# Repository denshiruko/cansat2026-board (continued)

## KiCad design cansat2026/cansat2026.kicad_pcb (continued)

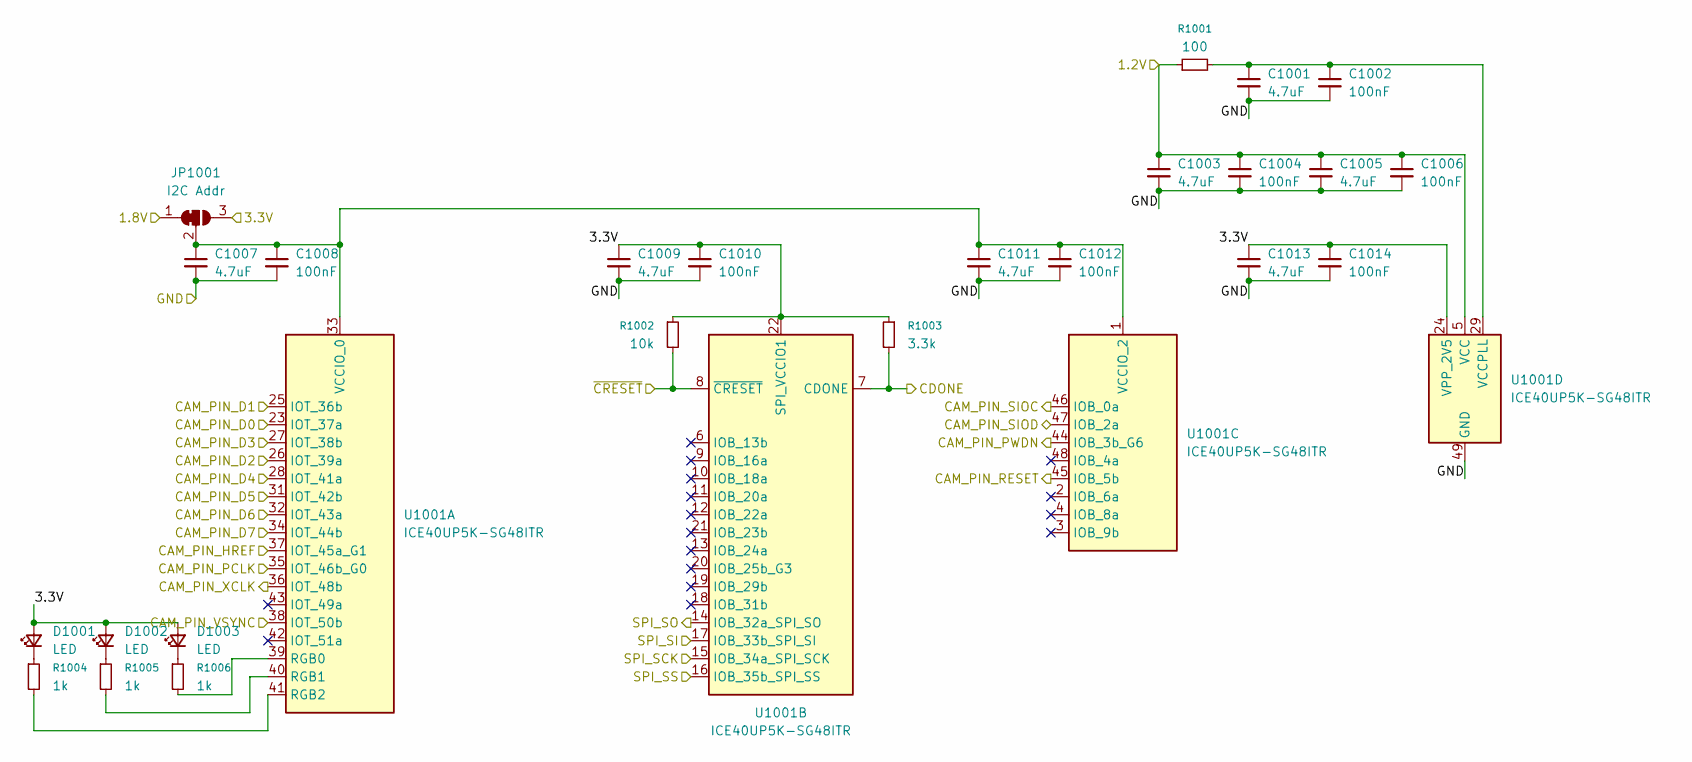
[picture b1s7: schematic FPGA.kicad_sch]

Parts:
C1001, C1003, C1005, C1007, C1009, C1011, C1013: 4.7uF; C_0402_1005Metric; LCSC Part C23733
C1002, C1004, C1006, C1008, C1010, C1012, C1014: 100nF; C_0402_1005Metric; LCSC Part C1525
D1001, D1002, D1003: LED; LED_0603_1608Metric
JP1001: I2C Addr; SolderJumper-3_P1.3mm_Bridged12_RoundedPad1.0x1.5mm_NumberL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
R1001: 100; R_0402_1005Metric; LCSC Part C25076
R1002: 10k; R_0402_1005Metric; LCSC Part C25744
R1003: 3.3k; R_0402_1005Metric; LCSC Part C25890
R1004, R1005, R1006: 1k; R_0402_1005Metric; LCSC Part C11702
U1001: ICE40UP5K-SG48ITR; QFN-48-1EP_7x7mm_P0.5mm_EP5.6x5.6mm; LCSC Part C2678152

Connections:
/1.2V: C1003.1, C1004.1, C1005.1, C1006.1, R1001.1, U1001.5 (VCC), U1001.30 (VCC); also elsewhere on the board
/1.8V: JP1001.1 (A); also elsewhere on the board
/CAM_PIN_D0: U1001.23 (IOT_37a); also elsewhere on the board
/CAM_PIN_D1: U1001.25 (IOT_36b); also elsewhere on the board
/CAM_PIN_D2: U1001.26 (IOT_39a); also elsewhere on the board
/CAM_PIN_D3: U1001.27 (IOT_38b); also elsewhere on the board
/CAM_PIN_D4: U1001.28 (IOT_41a); also elsewhere on the board
/CAM_PIN_D5: U1001.31 (IOT_42b); also elsewhere on the board
/CAM_PIN_D6: U1001.32 (IOT_43a); also elsewhere on the board
/CAM_PIN_D7: U1001.34 (IOT_44b); also elsewhere on the board
/CAM_PIN_HREF: U1001.37 (IOT_45a_G1); also elsewhere on the board
/CAM_PIN_PCLK: U1001.35 (IOT_46b_G0); also elsewhere on the board
/CAM_PIN_PWDN: U1001.44 (IOB_3b_G6); also elsewhere on the board
/CAM_PIN_RESET: U1001.45 (IOB_5b); also elsewhere on the board
/CAM_PIN_SIOC: U1001.46 (IOB_0a); also elsewhere on the board
/CAM_PIN_SIOD: U1001.47 (IOB_2a); also elsewhere on the board
/CAM_PIN_VSYNC: U1001.38 (IOT_50b); also elsewhere on the board
/CAM_PIN_XCLK: U1001.36 (IOT_48b); also elsewhere on the board
/MCU/FPGA_CDONE: R1003.2, U1001.7 (CDONE); also elsewhere on the board
/MCU/FPGA_SPI_MISO: U1001.14 (IOB_32a_SPI_SO); also elsewhere on the board
/MCU/FPGA_SPI_MOSI: U1001.17 (IOB_33b_SPI_SI); also elsewhere on the board
/MCU/FPGA_SPI_SCK: U1001.15 (IOB_34a_SPI_SCK); also elsewhere on the board
/MCU/FPGA_SPI_SS: U1001.16 (IOB_35b_SPI_SS); also elsewhere on the board
/MCU/FPGA_~CRESET: R1002.2, U1001.8 (~CRESET); also elsewhere on the board
/VCC: C1009.1, C1010.1, C1013.1, C1014.1, D1001.2 (A), D1002.2 (A), D1003.2 (A), JP1001.3 (B), R1002.1, R1003.1, U1001.22 (SPI_VCCIO1), U1001.24 (VPP_2V5); also elsewhere on the board
GND: C1001.2, C1002.2, C1003.2, C1004.2, C1005.2, C1006.2, C1007.2, C1008.2, C1009.2, C1010.2, C1011.2, C1012.2, C1013.2, C1014.2, U1001.49 (GND); also elsewhere on the board
unnamed: D1001.1 (K), R1004.1
unnamed: D1002.1 (K), R1005.1
unnamed: D1003.1 (K), R1006.1
unnamed: C1007.1, C1008.1, C1011.1, C1012.1, JP1001.2 (C), U1001.1 (VCCIO_2), U1001.33 (VCCIO_0)
unnamed: R1006.2, U1001.39 (RGB0)
unnamed: R1005.2, U1001.40 (RGB1)
unnamed: R1004.2, U1001.41 (RGB2)
unnamed: C1001.1, C1002.1, R1001.2, U1001.29 (VCCPLL)

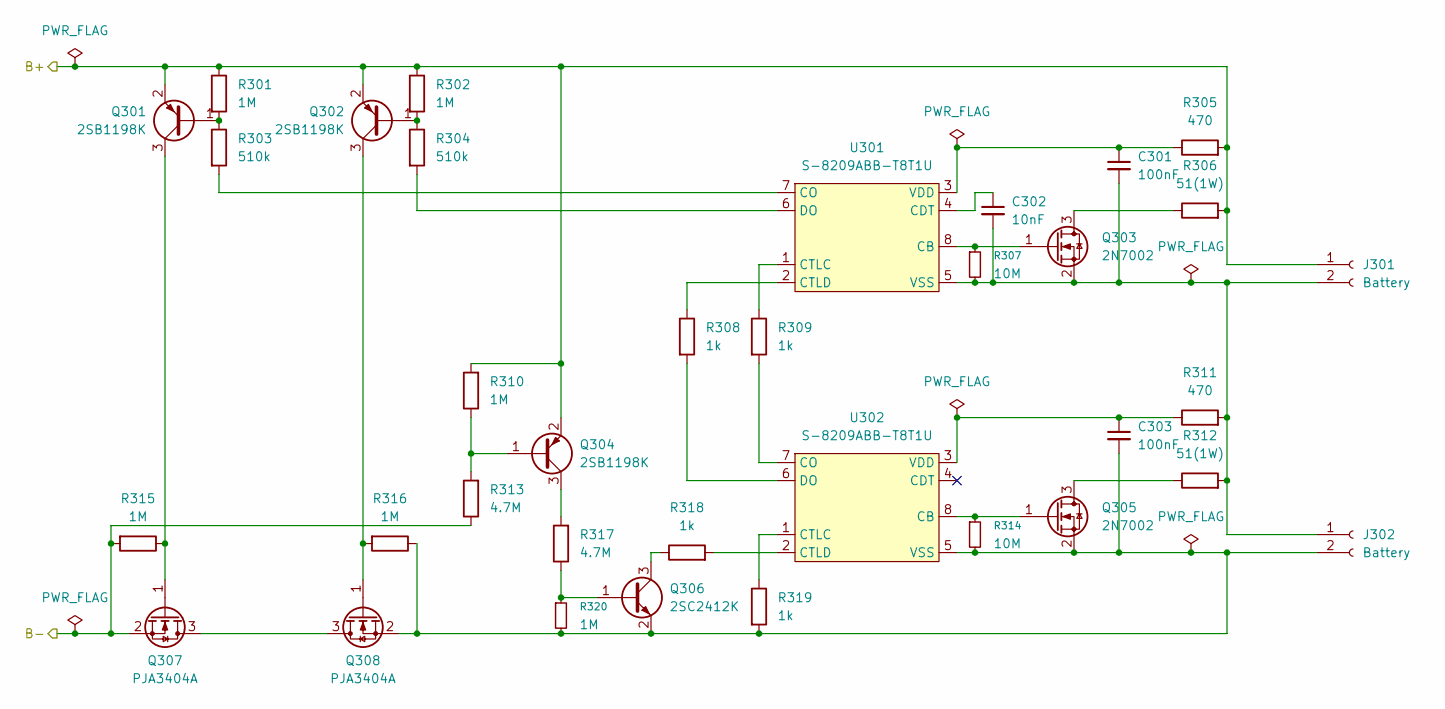
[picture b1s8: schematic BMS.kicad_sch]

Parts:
C301, C303: 100nF; C_0402_1005Metric; LCSC Part C1525
C302: 10nF; C_0402_1005Metric; LCSC Part C15195
J301, J302: Battery; JST_VH_B2P-VH_1x02_P3.96mm_Vertical
Q301, Q302, Q304: 2SB1198K; SC-59; LCSC Part C266246
Q303, Q305: 2N7002; SOT-23; LCSC Part C8545
Q306: 2SC2412K; SC-59; LCSC Part C111699
Q307, Q308: PJA3404A; SOT-23; Mouser Part 241-PJA3404AR100001
R301, R302, R310, R315, R316, R320: 1M; R_0402_1005Metric; LCSC Part C26083
R303, R304: 510k; R_0402_1005Metric; LCSC Part C11616
R305, R311: 470; R_0402_1005Metric; LCSC Part C25117
R306, R312: 51(1W); R_1206_3216Metric; Mouser Part 660-SG73S2BTTD51R0F
R307, R314: 10M; R_0603_1608Metric; LCSC Part C7250
R308, R309, R318, R319: 1k; R_0402_1005Metric; LCSC Part C11702
R313, R317: 4.7M; R_0603_1608Metric; LCSC Part C23163
U301, U302: S-8209ABB-T8T1U; TSSOP-8_4.4x3mm_P0.65mm; Mouser Part 628-S-8209ABB-T8T1U

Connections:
/Power/BATT+: J301.1, Q301.2, Q302.2, Q304.2, R301.1, R302.1, R305.2, R306.2, R310.2; also elsewhere on the board
GND: Q307.2 (S), R313.1, R315.2; also elsewhere on the board
unnamed: C301.2, C302.2, J301.2, J302.1, Q303.2 (S), R307.2, R311.2, R312.2, U301.5 (VSS)
unnamed: C303.2, J302.2, Q305.2 (S), Q306.2, Q308.2 (S), R314.2, R316.1, R319.2, R320.2, U302.5 (VSS)
unnamed: Q301.1, R301.2, R303.1
unnamed: Q302.1, R302.2, R304.1
unnamed: Q303.3 (D), R306.1
unnamed: Q303.1 (G), R307.1, U301.8 (CB)
unnamed: Q304.1, R310.1, R313.2
unnamed: Q304.3, R317.2
unnamed: Q305.3 (D), R312.1
unnamed: Q305.1 (G), R314.1, U302.8 (CB)
unnamed: Q306.1, R317.1, R320.1
unnamed: Q306.3, R318.1
unnamed: Q307.3 (D), Q308.3 (D)
unnamed: Q301.3, Q307.1 (G), R315.1
unnamed: Q302.3, Q308.1 (G), R316.2
unnamed: C302.1, U301.4 (CDT)
unnamed: R303.2, U301.7 (CO)
unnamed: R309.1, U301.1 (CTLC)
unnamed: R308.1, U301.2 (CTLD)
unnamed: R304.2, U301.6 (DO)
unnamed: C301.1, R305.1, U301.3 (VDD)
unnamed: R309.2, U302.7 (CO)
unnamed: R319.1, U302.1 (CTLC)
unnamed: R318.2, U302.2 (CTLD)
unnamed: R308.2, U302.6 (DO)
unnamed: C303.1, R311.1, U302.3 (VDD)

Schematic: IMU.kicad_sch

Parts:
C701, C702: 100nF; C_0402_1005Metric; LCSC Part C1525
JP701: I2C Addr; SolderJumper-3_P1.3mm_Bridged12_RoundedPad1.0x1.5mm_NumberL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
U701: LSM6DSV; LGA-14_3x2.5mm_P0.5mm_LayoutBorder3x4y

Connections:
/I2C1SCL: U701.13 (SCL); also elsewhere on the board
/I2C1SDA: U701.14 (SDA); also elsewhere on the board
/VCC: C701.1, C702.1, JP701.1 (A), U701.5 (VDDIO), U701.8 (VDD), U701.12 (CS); also elsewhere on the board
GND: C701.2, C702.2, JP701.3 (B), U701.2 (SDX), U701.3 (SCX), U701.6 (GND), U701.7 (GND); also elsewhere on the board
unnamed: JP701.2 (C), U701.1 (SDO/SA0)

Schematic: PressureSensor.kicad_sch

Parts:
C601: 100nF; C_0402_1005Metric; LCSC Part C1525
JP601: I2C Addr; SolderJumper-3_P1.3mm_Bridged12_RoundedPad1.0x1.5mm_NumberL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
U601: HP203B; LCSC Part C138665

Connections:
/I2C1SCL: U601.5 (SCL); also elsewhere on the board
/I2C1SDA: U601.6 (SDA); also elsewhere on the board
/VCC: C601.1, JP601.3 (B), U601.3 (VDD); also elsewhere on the board
GND: C601.2, JP601.1 (A), U601.2 (GND); also elsewhere on the board
unnamed: JP601.2 (C), U601.8 (CSB)

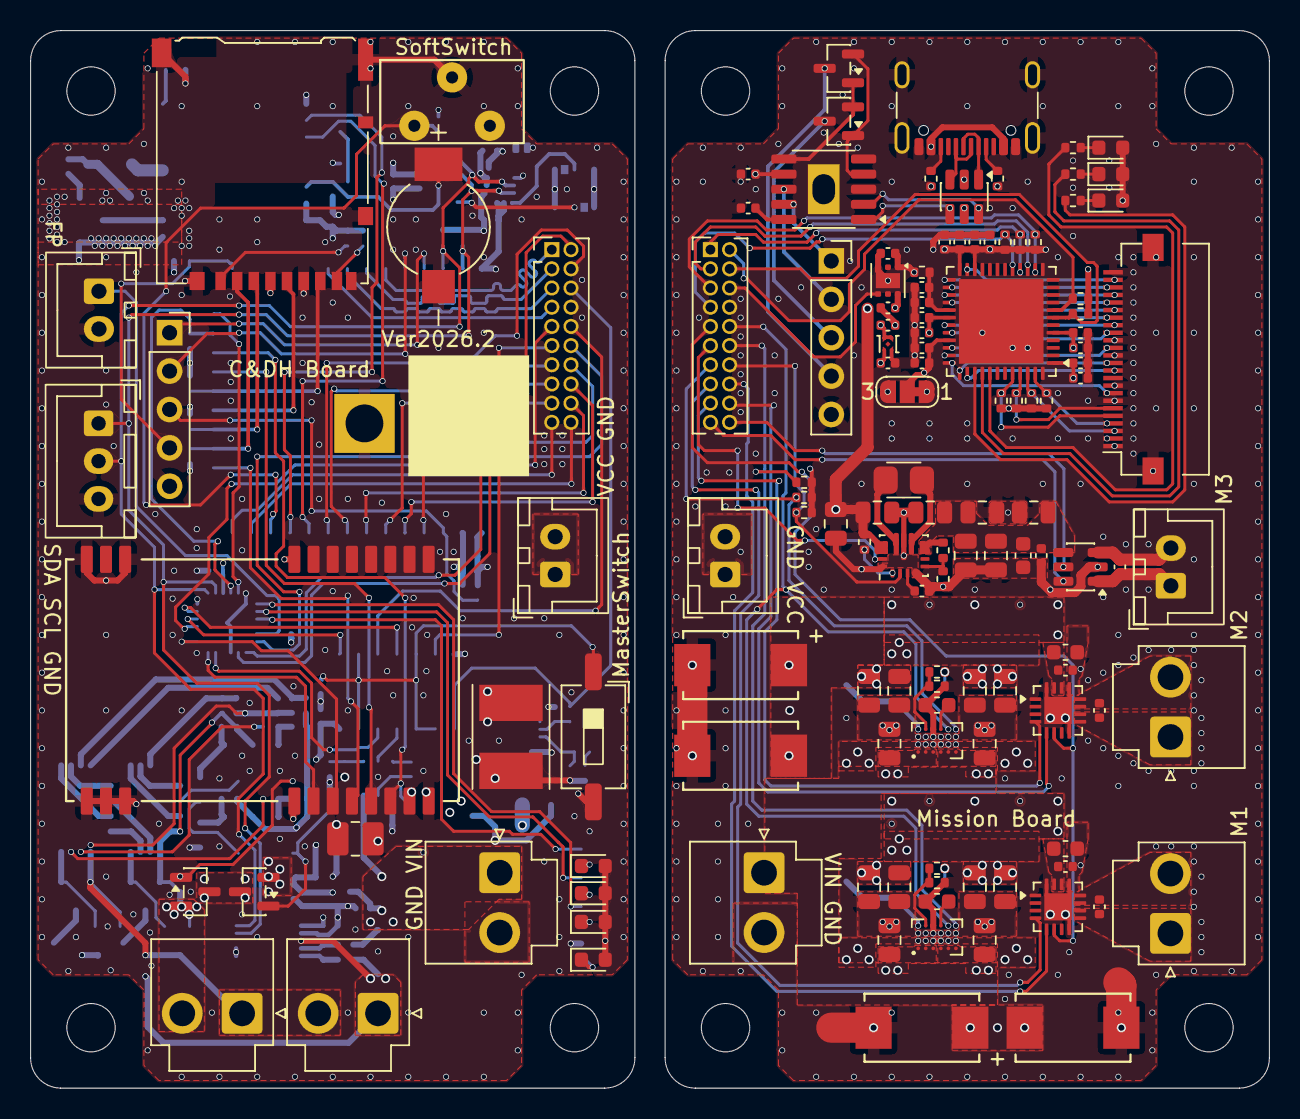
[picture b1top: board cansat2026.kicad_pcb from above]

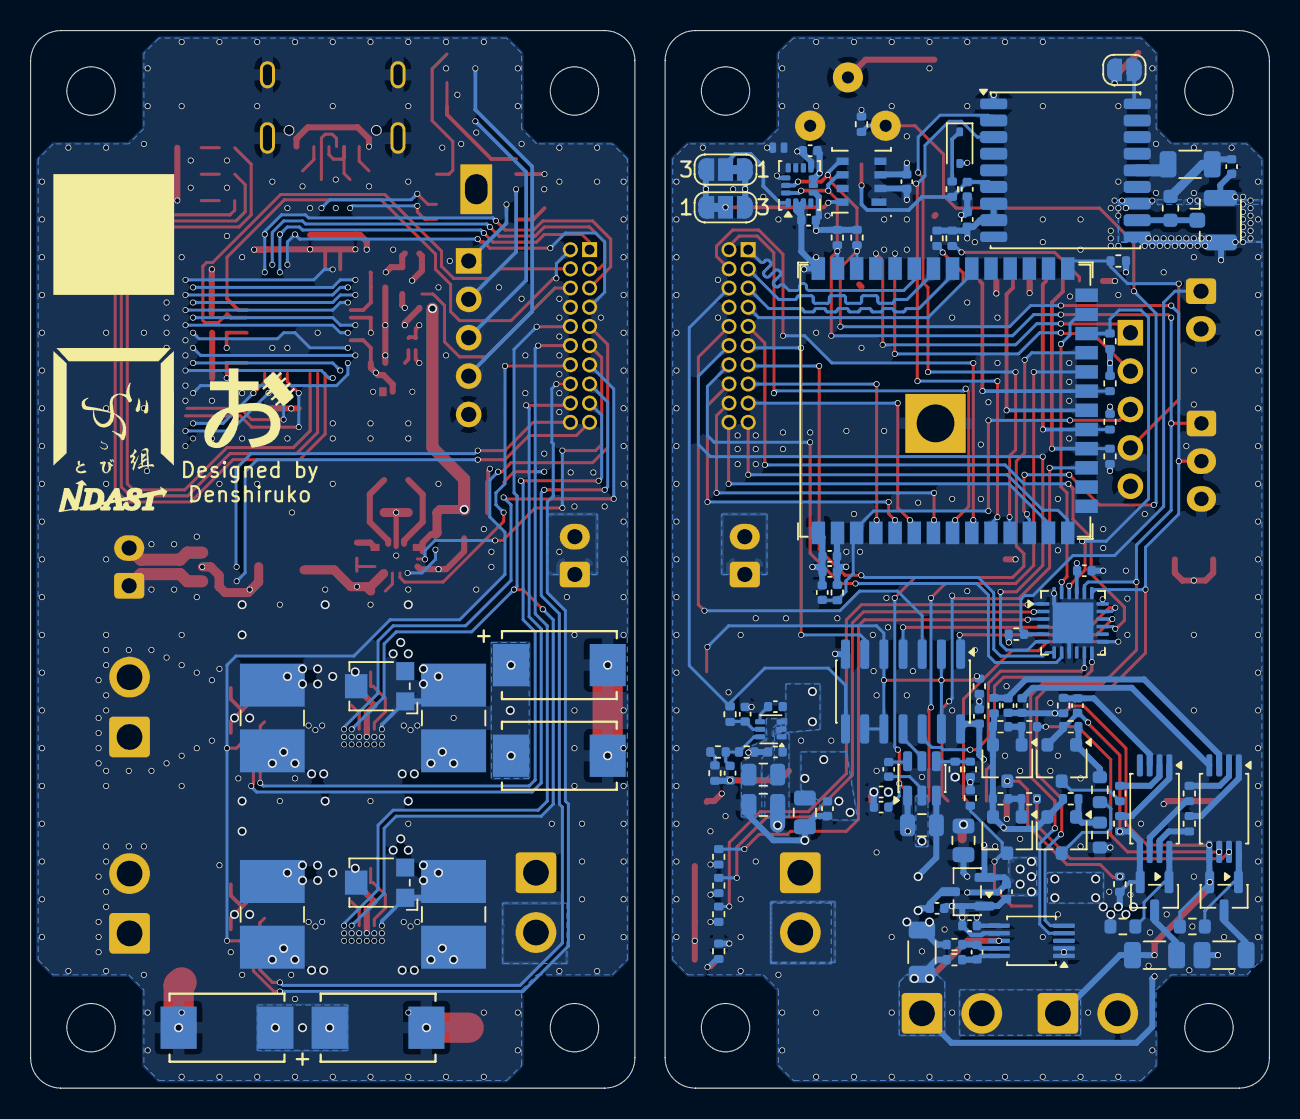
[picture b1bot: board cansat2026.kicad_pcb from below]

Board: 4 copper layers, 82.0 x 70.0 mm, 237 parts (113 on the bottom side), 164 nets.

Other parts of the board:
J101#2: MCU_UART_Conn; PinSocket_1x05_P2.54mm_Vertical

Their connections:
/EN: J101#2.3; also elsewhere on the board
/GPIO0: J101#2.4; also elsewhere on the board
/U0RXD: J101#2.2; also elsewhere on the board
/U0TXD: J101#2.1; also elsewhere on the board
GND: J101#2.5; also elsewhere on the board

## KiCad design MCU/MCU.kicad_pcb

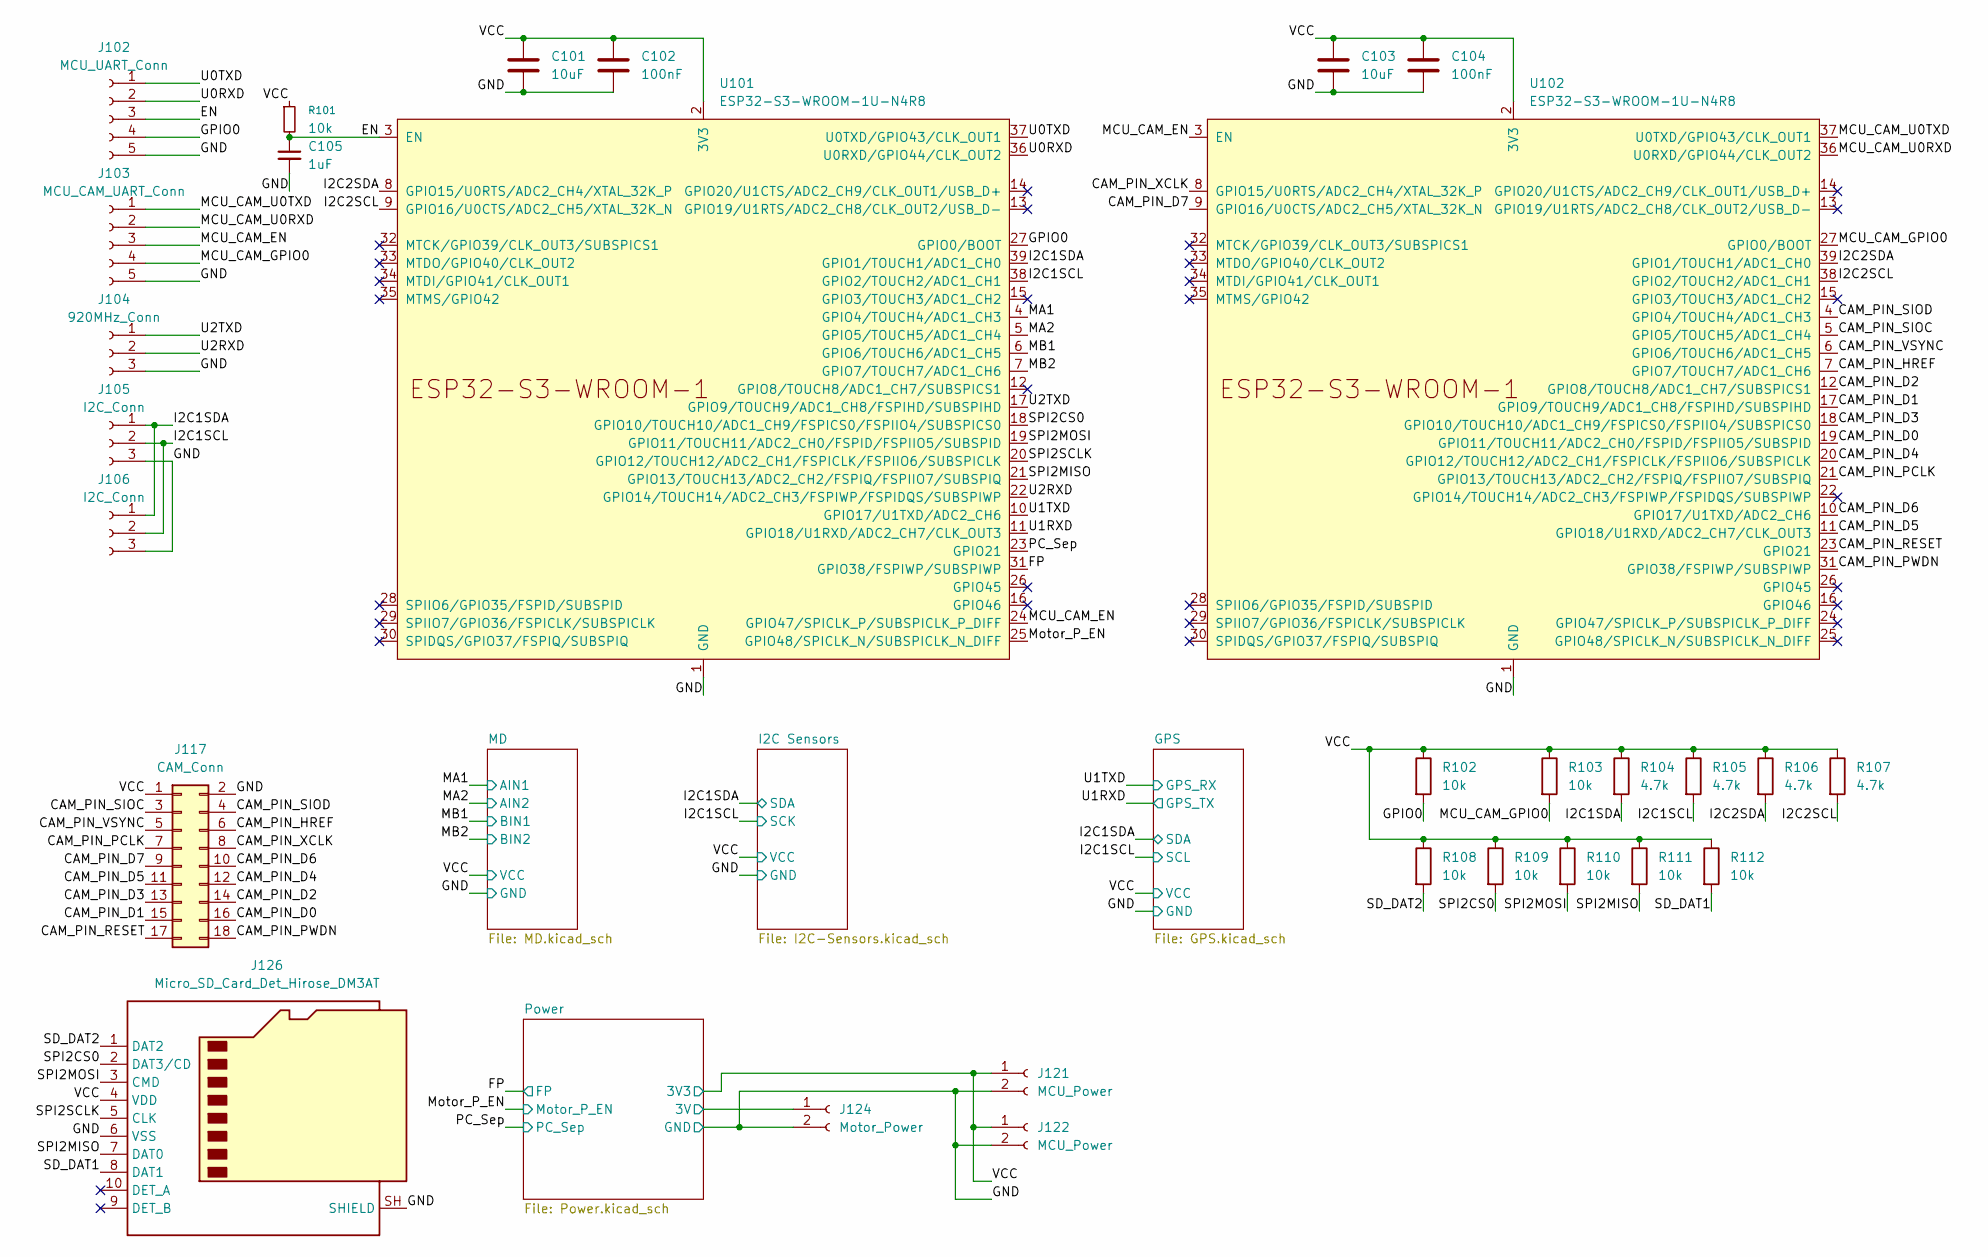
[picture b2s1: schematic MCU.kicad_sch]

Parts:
C101, C103: 10uF; C_0402_1005Metric; LCSC Part C15525
C102, C104: 100nF; C_0402_1005Metric; LCSC Part C1525
C105: 1uF; C_0402_1005Metric; LCSC Part C52923
J102: MCU_UART_Conn; PinSocket_1x05_P2.54mm_Vertical
J103: MCU_CAM_UART_Conn; PinSocket_1x05_P2.54mm_Vertical
J104: 920MHz_Conn; JST_XH_B3B-XH-A_1x03_P2.50mm_Vertical
J105, J106: I2C_Conn; JST_XH_B3B-XH-A_1x03_P2.50mm_Vertical
J117: CAM_Conn; PinHeader_2x10_P2.54mm_Vertical
J121, J122: MCU_Power; JST_XH_B2B-XH-A_1x02_P2.50mm_Vertical
J124: Motor_Power; JST_XH_B2B-XH-A_1x02_P2.50mm_Vertical
J126: Micro_SD_Card_Det_Hirose_DM3AT; microSD_HC_Hirose_DM3AT-SF-PEJM5
R101, R102, R103, R108, R109, R110, R111, R112: 10k; R_0402_1005Metric; LCSC Part C25744
R104, R105, R106, R107: 4.7k; R_0402_1005Metric; LCSC Part C25900
U101, U102: ESP32-S3-WROOM-1U-N4R8; ESP32-S3-WROOM-1U; Mouser Part 356-ESP32S3WRM1UN4R8; LCSC Part C3013943

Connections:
/CAM_PIN_D0: J117.16, U102.19 (GPIO11/TOUCH11/ADC2_CH0/FSPID/FSPIIO5/S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)
/CAM_PIN_D1: J117.15, U102.17 (GPIO9/TOUCH9/ADC1_CH8/FSPIHD/SUBSPIHD)
/CAM_PIN_D2: J117.14, U102.12 (GPIO8/TOUCH8/ADC1_CH7/SUBSPICS1)
/CAM_PIN_D3: J117.13, U102.18 (GPIO10/TOUCH10/ADC1_CH9/FSPICS0/FSPIIO4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)
/CAM_PIN_D4: J117.12, U102.20 (GPIO12/TOUCH12/ADC2_CH1/FSPICLK/FSPIIO6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)
/CAM_PIN_D5: J117.11, U102.11 (GPIO18/U1RXD/ADC2_CH7/CLK_OUT3)
/CAM_PIN_D6: J117.10, U102.10 (GPIO17/U1TXD/ADC2_CH6)
/CAM_PIN_D7: J117.9, U102.9 (GPIO16/U0CTS/ADC2_CH5/XTAL_32K_N)
/CAM_PIN_HREF: J117.6, U102.7 (GPIO7/TOUCH7/ADC1_CH6)
/CAM_PIN_PCLK: J117.7, U102.21 (GPIO13/TOUCH13/ADC2_CH2/FSPIQ/FSPIIO7/S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)
/CAM_PIN_PWDN: J117.18, U102.31 (GPIO38/FSPIWP/SUBSPIWP)
/CAM_PIN_RESET: J117.17, U102.23 (GPIO21)
/CAM_PIN_SIOC: J117.3, U102.5 (GPIO5/TOUCH5/ADC1_CH4)
/CAM_PIN_SIOD: J117.4, U102.4 (GPIO4/TOUCH4/ADC1_CH3)
/CAM_PIN_VSYNC: J117.5, U102.6 (GPIO6/TOUCH6/ADC1_CH5)
/CAM_PIN_XCLK: J117.8, U102.8 (GPIO15/U0RTS/ADC2_CH4/XTAL_32K_P)
/EN: C105.1, J102.3, R101.2, U101.3 (EN)
/FP: U101.31 (GPIO38/FSPIWP/SUBSPIWP); also elsewhere on the board
/GPIO0: J102.4, R102.2, U101.27 (GPIO0/BOOT)
/I2C1SCL: J105.2, J106.2, R105.2, U101.38 (GPIO2/TOUCH2/ADC1_CH1); also elsewhere on the board
/I2C1SDA: J105.1, J106.1, R104.2, U101.39 (GPIO1/TOUCH1/ADC1_CH0); also elsewhere on the board
/I2C2SCL: R107.2, U101.9 (GPIO16/U0CTS/ADC2_CH5/XTAL_32K_N), U102.38 (GPIO2/TOUCH2/ADC1_CH1)
/I2C2SDA: R106.2, U101.8 (GPIO15/U0RTS/ADC2_CH4/XTAL_32K_P), U102.39 (GPIO1/TOUCH1/ADC1_CH0)
/MA1: U101.4 (GPIO4/TOUCH4/ADC1_CH3); also elsewhere on the board
/MA2: U101.5 (GPIO5/TOUCH5/ADC1_CH4); also elsewhere on the board
/MB1: U101.6 (GPIO6/TOUCH6/ADC1_CH5); also elsewhere on the board
/MB2: U101.7 (GPIO7/TOUCH7/ADC1_CH6); also elsewhere on the board
/MCU_CAM_EN: J103.3, U101.24 (GPIO47/SPICLK_P/SUBSPICLK_P_DIFF), U102.3 (EN)
/MCU_CAM_GPIO0: J103.4, R103.2, U102.27 (GPIO0/BOOT)
/MCU_CAM_U0RXD: J103.2, U102.36 (U0RXD/GPIO44/CLK_OUT2)
/MCU_CAM_U0TXD: J103.1, U102.37 (U0TXD/GPIO43/CLK_OUT1)
/Motor_P_EN: U101.25 (GPIO48/SPICLK_N/SUBSPICLK_N_DIFF); also elsewhere on the board
/PC_Sep: U101.23 (GPIO21); also elsewhere on the board
/Power/3V: J124.1; also elsewhere on the board
/SD_DAT1: J126.8 (DAT1), R112.2
/SD_DAT2: J126.1 (DAT2), R108.2
/SPI2CS0: J126.2 (DAT3/CD), R109.2, U101.18 (GPIO10/TOUCH10/ADC1_CH9/FSPICS0/FSPIIO4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)
/SPI2MISO: J126.7 (DAT0), R111.2, U101.21 (GPIO13/TOUCH13/ADC2_CH2/FSPIQ/FSPIIO7/S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)
/SPI2MOSI: J126.3 (CMD), R110.2, U101.19 (GPIO11/TOUCH11/ADC2_CH0/FSPID/FSPIIO5/S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)
/SPI2SCLK: J126.5 (CLK), U101.20 (GPIO12/TOUCH12/ADC2_CH1/FSPICLK/FSPIIO6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)
/U0RXD: J102.2, U101.36 (U0RXD/GPIO44/CLK_OUT2)
/U0TXD: J102.1, U101.37 (U0TXD/GPIO43/CLK_OUT1)
/U1RXD: U101.11 (GPIO18/U1RXD/ADC2_CH7/CLK_OUT3); also elsewhere on the board
/U1TXD: U101.10 (GPIO17/U1TXD/ADC2_CH6); also elsewhere on the board
/U2RXD: J104.2, U101.22 (GPIO14/TOUCH14/ADC2_CH3/FSPIWP/FSPIDQS/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)
/U2TXD: J104.1, U101.17 (GPIO9/TOUCH9/ADC1_CH8/FSPIHD/SUBSPIHD)
/VCC: C101.1, C102.1, C103.1, C104.1, J117.1, J121.1, J122.1, J126.4 (VDD), R101.1, R102.1, R103.1, R104.1, R105.1, R106.1, R107.1, R108.1, R109.1, R110.1, R111.1, R112.1, U101.2 (3V3), U102.2 (3V3); also elsewhere on the board
GND: C101.2, C102.2, C103.2, C104.2, C105.2, J102.5, J103.5, J104.3, J105.3, J106.3, J117.2, J121.2, J122.2, J124.2, J126.6 (VSS), J126.SH (SHIELD), U101.1 (GND), U101.40 (GND), U101.41 (GND), U102.1 (GND), U102.40 (GND), U102.41 (GND); also elsewhere on the board

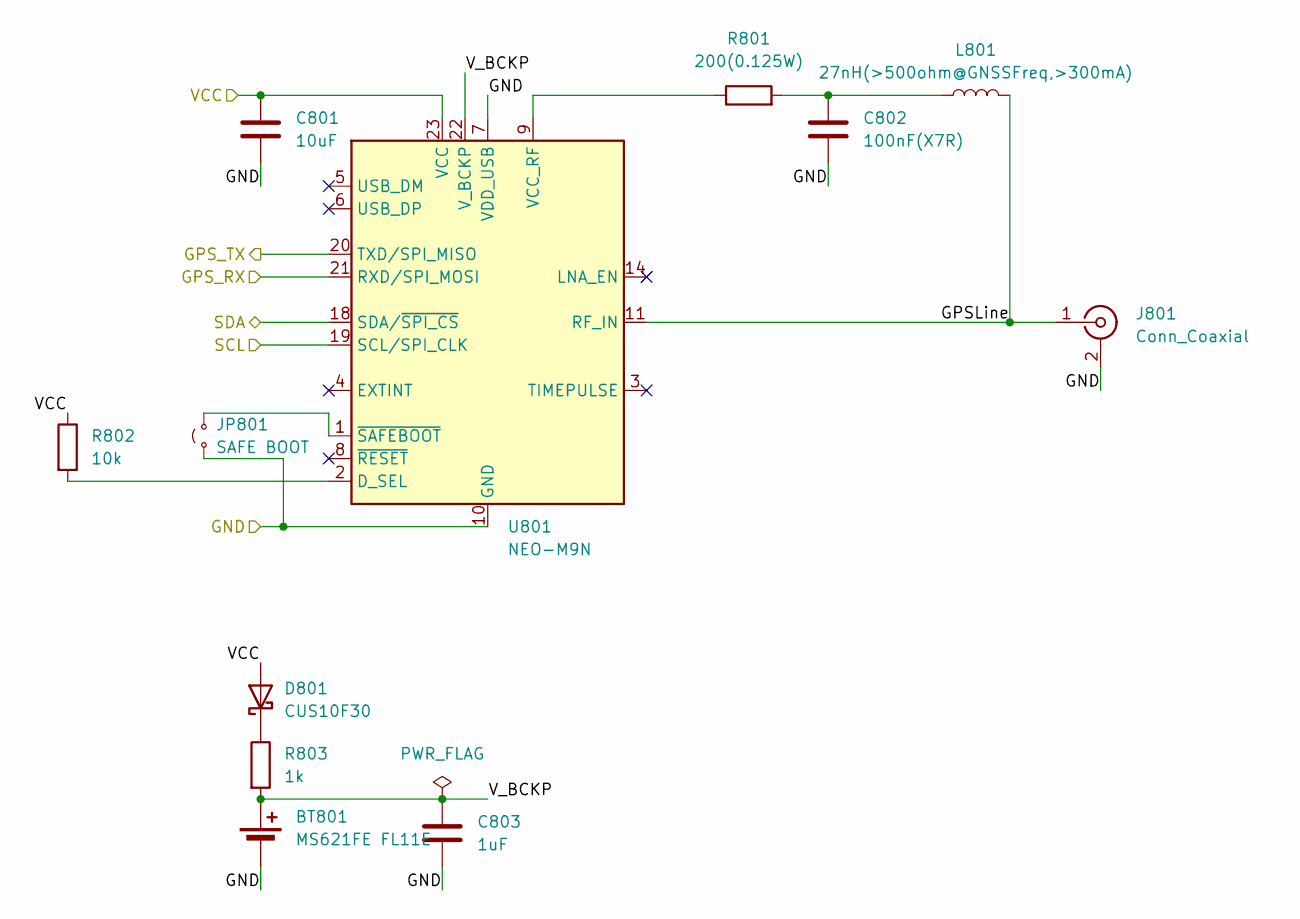
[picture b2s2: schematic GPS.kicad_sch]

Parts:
BT801: MS621FE FL11E; BatteryHolder_Seiko_MS621F
C801: 10uF; C_0402_1005Metric; LCSC Part C15525
C802: 100nF(X7R); C_0402_1005Metric; LCSC Part C1525
C803: 1uF; C_0402_1005Metric; LCSC Part C52923
D801: CUS10F30; D_SOD-323
J801: Conn_Coaxial; SMA_Amphenol_132134-11_Vertical
JP801: SAFE BOOT; SolderJumper-2_P1.3mm_Open_RoundedPad1.0x1.5mm
L801: 27nH(>500ohm@GNSSFreq,>300mA); L_0603_1608Metric; Mouser Part 710-7447860127G
R801: 200(0.125W); R_0805_2012Metric; LCSC Part C17540
R802: 10k; R_0402_1005Metric; LCSC Part C25744
R803: 1k; R_0402_1005Metric; LCSC Part C11702
U801: NEO-M9N; ublox_NEO; Mouser Part 377-NEO-M9N-00B

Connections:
/GPS/GPSLine: J801.1 (In), L801.2, U801.11 (RF_IN)
/GPS/V_BCKP: BT801.1 (+), C803.1, R803.2, U801.22 (V_BCKP)
/I2C1SCL: U801.19 (SCL/SPI_CLK); also elsewhere on the board
/I2C1SDA: U801.18 (SDA/~SPI_CS); also elsewhere on the board
/U1RXD: U801.20 (TXD/SPI_MISO); also elsewhere on the board
/U1TXD: U801.21 (RXD/SPI_MOSI); also elsewhere on the board
/VCC: C801.1, D801.2 (A), R802.1, U801.23 (VCC); also elsewhere on the board
GND: BT801.2 (-), C801.2, C802.2, C803.2, J801.2 (Ext), JP801.1 (A), U801.7 (VDD_USB), U801.10 (GND), U801.12 (GND), U801.13 (GND), U801.24 (GND); also elsewhere on the board
unnamed: C802.1, L801.1, R801.2
unnamed: D801.1 (K), R803.1
unnamed: JP801.2 (B), U801.1 (~SAFEBOOT)
unnamed: R802.2, U801.2 (D_SEL)
unnamed: R801.1, U801.9 (VCC_RF)

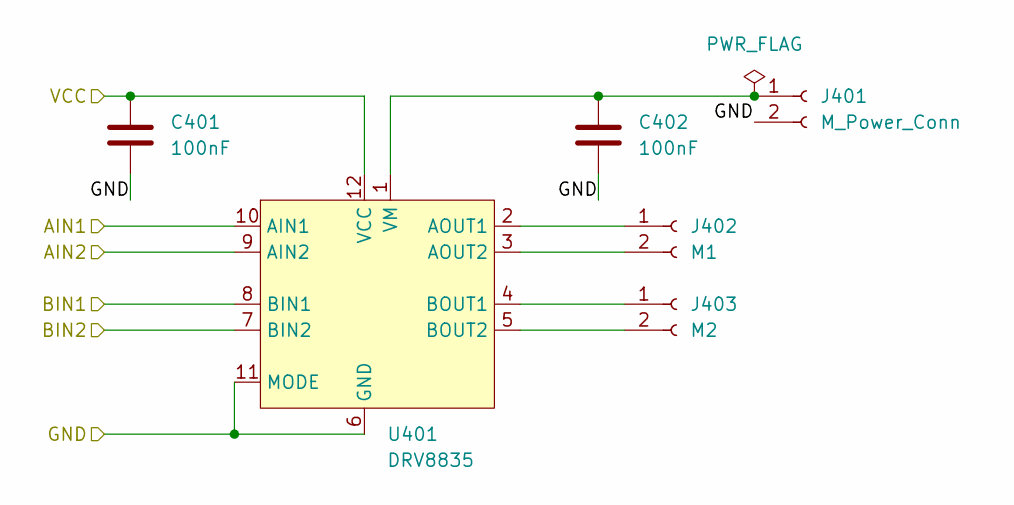
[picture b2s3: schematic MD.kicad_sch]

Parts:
C401, C402: 100nF; C_0402_1005Metric; LCSC Part C1525
J401: M_Power_Conn; JST_XH_B2B-XH-A_1x02_P2.50mm_Vertical
J402: M1; JST_XH_B2B-XH-A_1x02_P2.50mm_Vertical
J403: M2; JST_XH_B2B-XH-A_1x02_P2.50mm_Vertical
U401: DRV8835; WSON-12-1EP_3x2mm_P0.5mm_EP1x2.65_ThermalVias; LCSC Part C129328

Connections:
/MA1: U401.10 (AIN1); also elsewhere on the board
/MA2: U401.9 (AIN2); also elsewhere on the board
/MB1: U401.8 (BIN1); also elsewhere on the board
/MB2: U401.7 (BIN2); also elsewhere on the board
/VCC: C401.1, U401.12 (VCC); also elsewhere on the board
GND: C401.2, C402.2, J401.2, U401.6 (GND), U401.11 (MODE), U401.13; also elsewhere on the board
unnamed: C402.1, J401.1, U401.1 (VM)
unnamed: J402.1, U401.2 (AOUT1)
unnamed: J402.2, U401.3 (AOUT2)
unnamed: J403.1, U401.4 (BOUT1)
unnamed: J403.2, U401.5 (BOUT2)

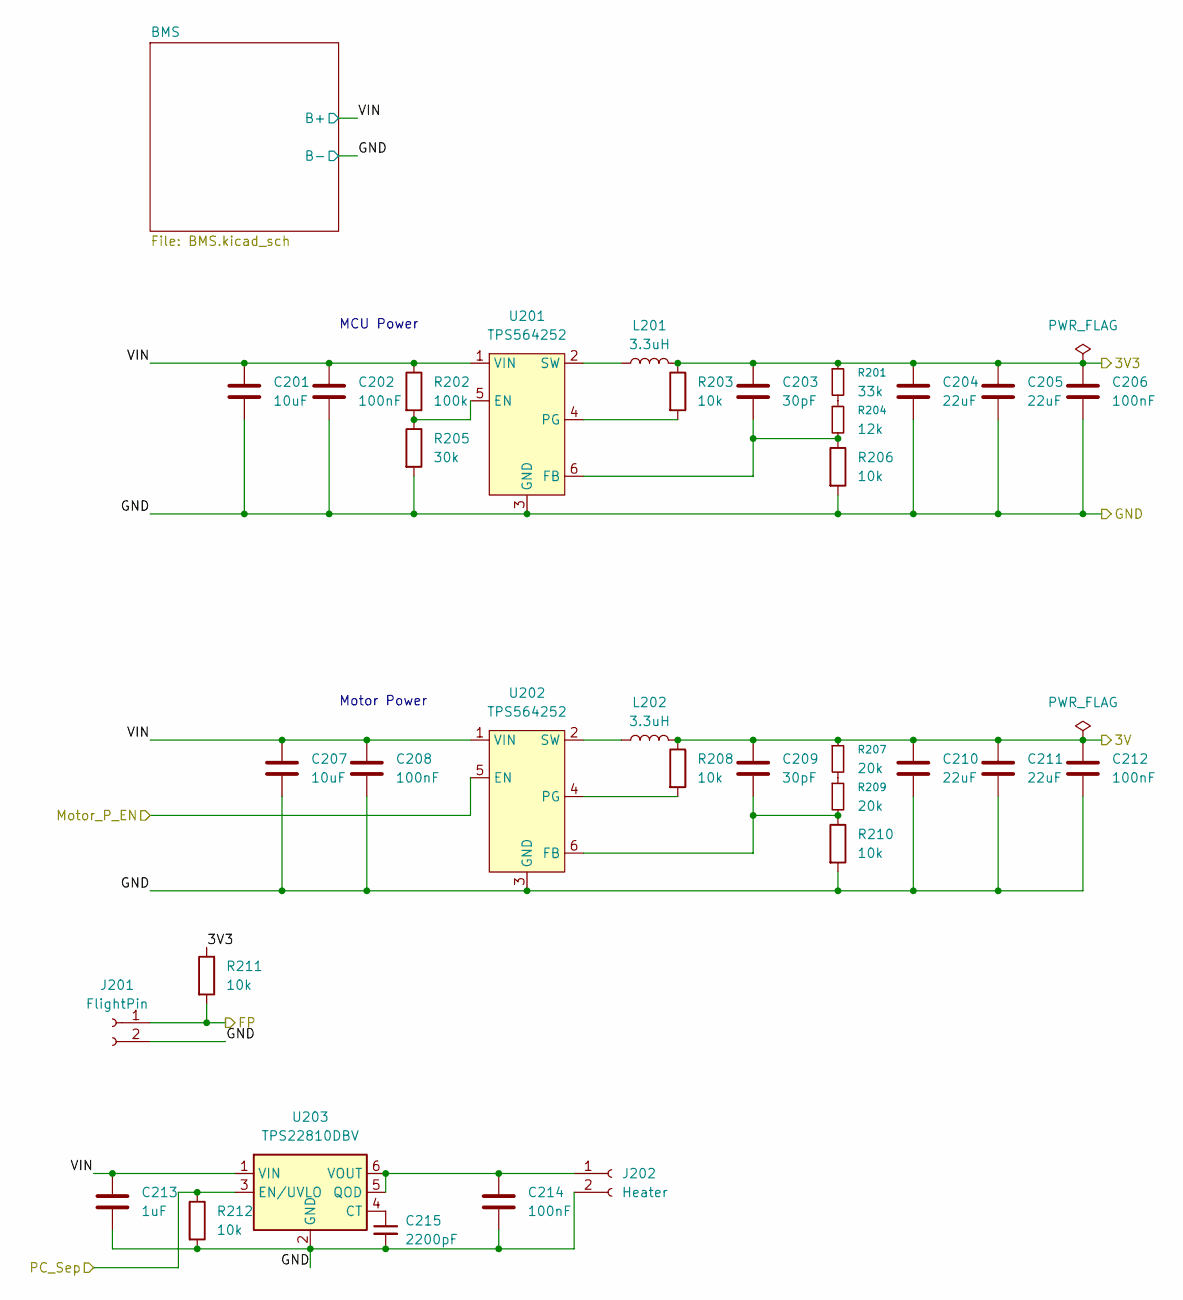
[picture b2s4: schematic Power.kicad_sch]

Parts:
C201, C207: 10uF; C_0805_2012Metric; LCSC Part C15850
C202, C208, C214: 100nF; C_0603_1608Metric; LCSC Part C14663
C203, C209: 30pF; C_0402_1005Metric; LCSC Part C1570
C204, C205, C210, C211: 22uF; C_0805_2012Metric; LCSC Part C45783
C206, C212: 100nF; C_0402_1005Metric; LCSC Part C1525
C213: 1uF; C_0402_1005Metric; LCSC Part C52923
C215: 2200pF; C_0402_1005Metric; LCSC Part C1531
J201: FlightPin; JST_XH_B2B-XH-A_1x02_P2.50mm_Vertical
J202: Heater; TerminalBlock_Phoenix_MKDS-1,5-2-5.08_1x02_P5.08mm_Horizont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
L201, L202: 3.3uH; L_TDK_VLS6045EX_VLS6045AF; Mouser Part 810-VLS6045EX-3R3N
R201: 33k; R_0402_1005Metric; LCSC Part C25779
R202: 100k; R_0402_1005Metric; LCSC Part C25741
R203, R206, R208, R210, R211, R212: 10k; R_0402_1005Metric; LCSC Part C25744
R204: 12k; R_0402_1005Metric; LCSC Part C25752
R205: 30k; R_0603_1608Metric; LCSC Part C22984
R207, R209: 20k; R_0402_1005Metric; LCSC Part C25765
U201, U202: TPS564252; SOT-563; Mouser Part 595-TPS564252DRLR; LCSC Part C19191267
U203: TPS22810DBV; SOT-23-6; Mouser Part 595-TPS22810DBVR; LCSC Part C2680364

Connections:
/FP: J201.1, R211.2; also elsewhere on the board
/Motor_P_EN: U202.5 (EN); also elsewhere on the board
/PC_Sep: R212.1, U203.3 (EN/UVLO); also elsewhere on the board
/Power/3V: C209.1, C210.1, C211.1, C212.1, L202.2, R207.1, R208.1; also elsewhere on the board
/Power/VIN: C201.1, C202.1, C207.1, C208.1, C213.1, R202.1, U201.1 (VIN), U202.1 (VIN), U203.1 (VIN); also elsewhere on the board
/VCC: C203.1, C204.1, C205.1, C206.1, L201.2, R201.1, R203.1, R211.1; also elsewhere on the board
GND: C201.2, C202.2, C204.2, C205.2, C206.2, C207.2, C208.2, C210.2, C211.2, C212.2, C213.2, C214.2, C215.2, J201.2, J202.2, R205.2, R206.2, R210.2, R212.2, U201.3 (GND), U202.3 (GND), U203.2 (GND); also elsewhere on the board
unnamed: C214.1, J202.1, U203.5 (QOD), U203.6 (VOUT)
unnamed: R201.2, R204.1
unnamed: R207.2, R209.1
unnamed: R202.2, R205.1, U201.5 (EN)
unnamed: C203.2, R204.2, R206.1, U201.6 (FB)
unnamed: R203.2, U201.4 (PG)
unnamed: L201.1, U201.2 (SW)
unnamed: C209.2, R209.2, R210.1, U202.6 (FB)
unnamed: R208.2, U202.4 (PG)
unnamed: L202.1, U202.2 (SW)
unnamed: C215.1, U203.4 (CT)

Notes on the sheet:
MCU Power
Motor Power

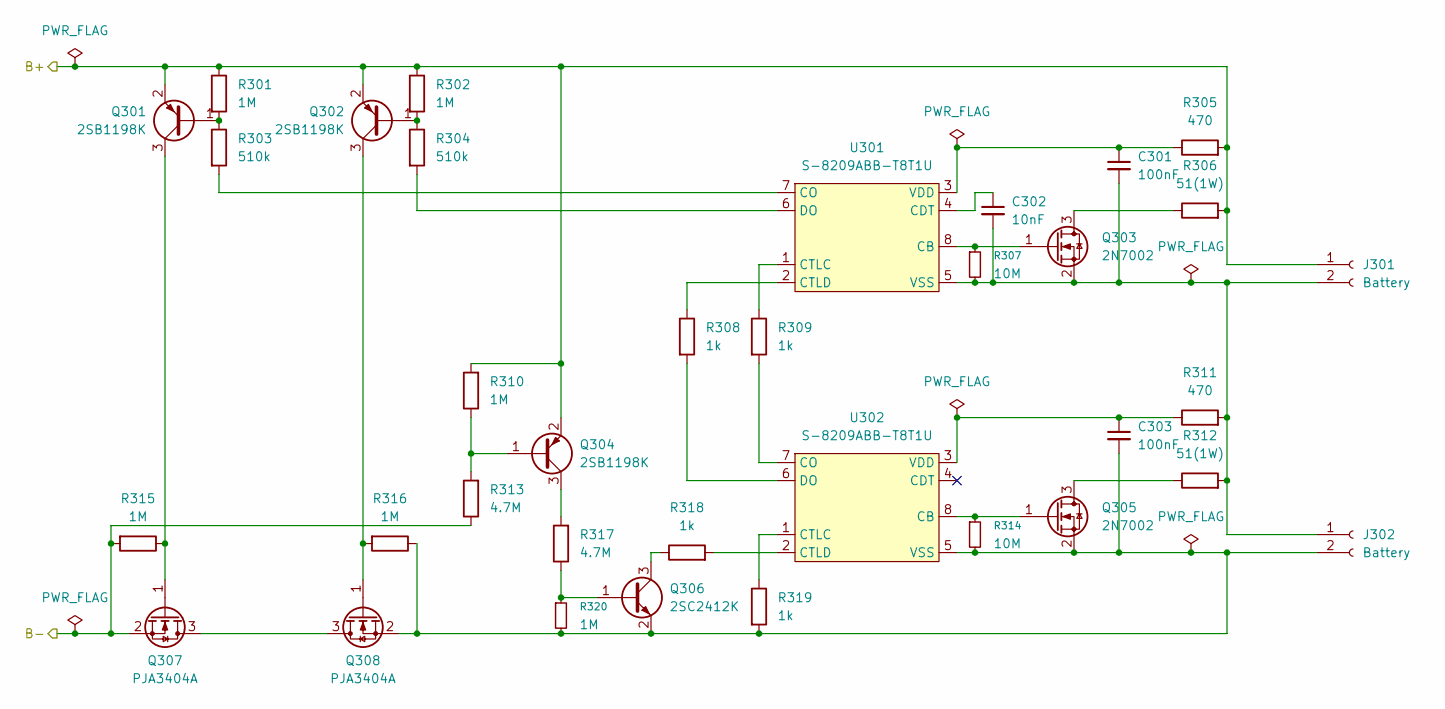
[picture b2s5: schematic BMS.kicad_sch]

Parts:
C301, C303: 100nF; C_0603_1608Metric; LCSC Part C14663
C302: 10nF; C_0402_1005Metric; LCSC Part C15195
J301, J302: Battery; JST_XH_B2B-XH-A_1x02_P2.50mm_Vertical
Q301, Q302, Q304: 2SB1198K; SC-59; Mouser Part 755-2SB1198KT146R; LCSC Part C266246
Q303, Q305: 2N7002; SOT-23; LCSC Part C8545
Q306: 2SC2412K; SC-59; Mouser Part 755-2SC2412KT146R; LCSC Part C111699
Q307, Q308: PJA3404A; SOT-23; Mouser Part 241-PJA3404AR100001
R301, R302, R310, R315, R316, R320: 1M; R_0402_1005Metric; LCSC Part C26083
R303, R304: 510k; R_0402_1005Metric; LCSC Part C11616
R305, R311: 470; R_0402_1005Metric; LCSC Part C25117
R306, R312: 51(1W); R_1206_3216Metric; Mouser Part 660-SG73S2BTTD51R0F
R307, R314: 10M; R_0402_1005Metric; LCSC Part C26082
R308, R309, R318, R319: 1k; R_0402_1005Metric; LCSC Part C11702
R313, R317: 4.7M; R_0603_1608Metric; LCSC Part C23163
U301, U302: S-8209ABB-T8T1U; TSSOP-8_4.4x3mm_P0.65mm; Mouser Part 628-S-8209ABB-T8T1U

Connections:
/Power/VIN: J301.1, Q301.2, Q302.2, Q304.2, R301.1, R302.1, R305.2, R306.2, R310.2; also elsewhere on the board
GND: Q307.2 (S), R313.1, R315.2; also elsewhere on the board
unnamed: C301.2, C302.2, J301.2, J302.1, Q303.2 (S), R307.2, R311.2, R312.2, U301.5 (VSS)
unnamed: C303.2, J302.2, Q305.2 (S), Q306.2, Q308.2 (S), R314.2, R316.1, R319.2, R320.2, U302.5 (VSS)
unnamed: Q301.1, R301.2, R303.1
unnamed: Q302.1, R302.2, R304.1
unnamed: Q303.3 (D), R306.1
unnamed: Q303.1 (G), R307.1, U301.8 (CB)
unnamed: Q304.1, R310.1, R313.2
unnamed: Q304.3, R317.2
unnamed: Q305.3 (D), R312.1
unnamed: Q305.1 (G), R314.1, U302.8 (CB)
unnamed: Q306.1, R317.1, R320.1
unnamed: Q306.3, R318.1
unnamed: Q307.3 (D), Q308.3 (D)
unnamed: Q301.3, Q307.1 (G), R315.1
unnamed: Q302.3, Q308.1 (G), R316.2
unnamed: C302.1, U301.4 (CDT)
unnamed: R303.2, U301.7 (CO)
unnamed: R309.1, U301.1 (CTLC)
unnamed: R308.1, U301.2 (CTLD)
unnamed: R304.2, U301.6 (DO)
unnamed: C301.1, R305.1, U301.3 (VDD)
unnamed: R309.2, U302.7 (CO)
unnamed: R319.1, U302.1 (CTLC)
unnamed: R318.2, U302.2 (CTLD)
unnamed: R308.2, U302.6 (DO)
unnamed: C303.1, R311.1, U302.3 (VDD)

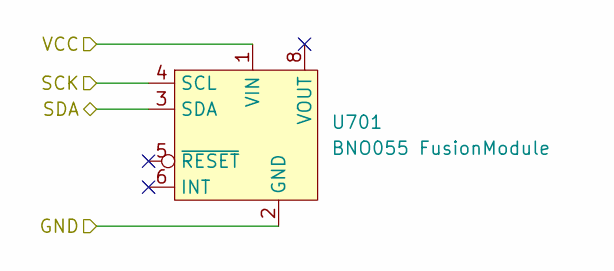
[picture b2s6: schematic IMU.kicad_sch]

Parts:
U701: BNO055 FusionModule; BNO055-FusionModule

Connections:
/I2C1SCL: U701.4 (SCL); also elsewhere on the board
/I2C1SDA: U701.3 (SDA); also elsewhere on the board
/VCC: U701.1 (VIN); also elsewhere on the board
GND: U701.2 (GND), U701.7 (GND); also elsewhere on the board
